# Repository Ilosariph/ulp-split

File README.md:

# ULP Split

Wireless split keyboard: 25 keys per half (6 columns, 4/4/4/4/3/3 + 3 thumbs), choc spacing (18 x 17 mm),
Cherry MX ULP switches (through-hole, double-sided footprint), Seeed XIAO nRF52840, ZMK.

## Layout

```
pcb/        ergogen config, footprints, autorouting + Gerber build
config/     ZMK keymap + conf (Colemak-DH-ish + Swiss German, ported from the tightarc Vial layout)
boards/     ZMK shield ulp_split (left = central)
case/       OpenSCAD tray case with 401525 LiPo pocket
```

## PCB

`pcb/build.sh` runs ergogen, autoroutes both halves with Freerouting, runs DRC and writes JLCPCB zips:

- `pcb/build/{left,right}.kicad_pcb` routed boards
- `pcb/build/jlcpcb-{left,right}.zip` Gerbers + drill

JLCPCB: 2 layers, 0.6 mm, LeadFree HASL, tented vias, Remove Mark.

Parts per half: 25 Cherry MX ULP, 25 1N4148WS (SOD-323, LCSC C2128), XIAO nRF52840, C&K PCM12SMTR power switch,
Molex 78171-0002 Pico-EZmate header + 36920-0200 cable (cut in half), LiPo with protection circuit (401525).
Trackpad half: 2x 4.7k 0805 (R1, R2).

Diodes sit on top, outside every keycap (strips at the column ends, beside the inner column, thumb gap), each
labelled with its key (column O/P/R/M/I/N/T + row T/H/B/L, thumbs TN/TM/TF; bar = cathode). The bottom only has
solder from the switch, battery and NFC pads. `pcb/place_diodes.py` picks the spots (>= 0.25 mm from the keycap
outlines, both halves) and rewrites the generated block in `config.yaml`; rerun it after `build.sh` when keys or parts
move, then build again.
Backup: SOD-123 pads (1N4148W, `DB*`) on the back under each switch, in parallel with the top diode. Fit one diode
per key. Back diodes need the 2 mm gap under the PCB; under the index-bottom and inner-home keys they sit close to
the `mount_opt` bosses, print the case with `use_opt = false` if you use those two.

## Case

`case/case.scad`: 4.8 mm tall tray (1.2 floor, 2 mm under the PCB, 0.6 PCB, 1 mm lip). The PCB drops in on a perimeter
ledge + a post under each key and is screwed down from the top: M2 x 4 screws into heat-set inserts (M2 x 3, 3.2 mm OD)
in bosses under the board (`screw_hole = 1.7` for self-tapping instead).
9 holes have the screw head clear of the keycaps (small tabs on the outer edge, gap above the thumbs, controller column).
7 more (`mount_opt_*`) sit between switch housings under the keycaps: only for low heads (wafer / ISO 7380), check
keycap clearance first; `use_opt = false` drops their bosses. The 401525 LiPo sits in its own pocket in the
notch between the far thumb key and the bottom of the controller column. The battery connector sits at the bottom edge of
the controller column with its plug facing the notch, so the wires drop straight into the pocket (no cable hole).
The notch takes a cell up to ~25 x 26 x 4 mm: set `bat` in `case.scad`. Openings for USB-C and the power switch lever.

```
openscad -o left.stl case/case.scad
openscad -D 'side="right"' -o right.stl case/case.scad
```

`case/pcb_left.dxf` is a copy of `pcb/output/outlines/left.dxf`; copy it again after changing the board outline.

## Matrix

col2row, 5 x 5 on D0..D9. Columns D0..D4 = outer, pinky, ring, middle, index.
Rows D7 top, D8 home, D9 bottom, D6 lower (outer 4 columns + near thumb on D4), D5 extra
(inner top/home/bottom on D3/D4/D2, mid thumb on D1, far thumb on D0).
D10 and the XIAO's NFC pads (NFC1 = P0.09, NFC2 = P0.10, plated through like the battery pads) drive the trackpad.

## Trackpad

Right half (firmware), pads on both: TP1 below the XIAO, 1x5 2.54 mm, GND / 3V3 / DR / SDA / SCL.
SDA = NFC1, SCL = NFC2 (UICR `nfct-pins-as-gpios`), DR = D10, R1/R2 = 4.7k 0805 pull-ups to 3V3.
Firmware: Cirque Pinnacle (`cirque,pinnacle` from petejohanson/cirque-input-module, I2C 0x2A) on the right half,
forwarded to the left through `zmk,input-split`. A TM040040 runs in I2C mode with R1 not fitted; wire VDD, GND, SCL,
SDA and DR from its test pads straight to TP1 (skip 5 V adapter boards). An Azoteq IQS5xx pad (TPS43/TPS65) fits
the same pads (RDY on DR, NRST tied to 3V3) with an IQS5xx driver module instead.

## Firmware

GitHub Actions builds `ulp_split_left`, `ulp_split_right` and `settings_reset` for `seeeduino_xiao_ble` (ZMK v0.3).
Flash: double-tap reset, copy the uf2 to the XIAO drive. Edit the keymap with https://nickcoutsos.github.io/keymap-editor.

The battery charges over USB only while the power switch is on (the switch sits between battery and XIAO).

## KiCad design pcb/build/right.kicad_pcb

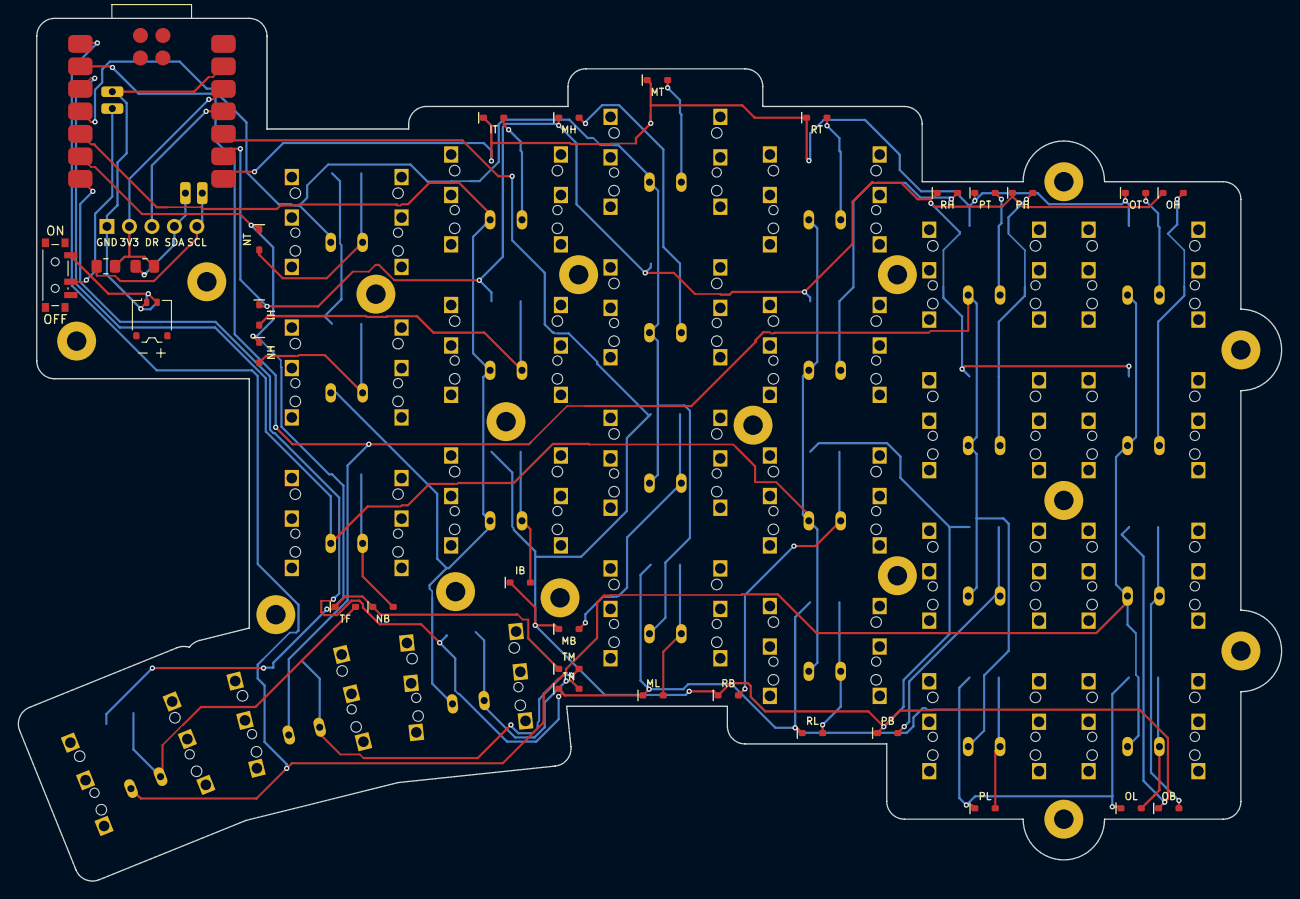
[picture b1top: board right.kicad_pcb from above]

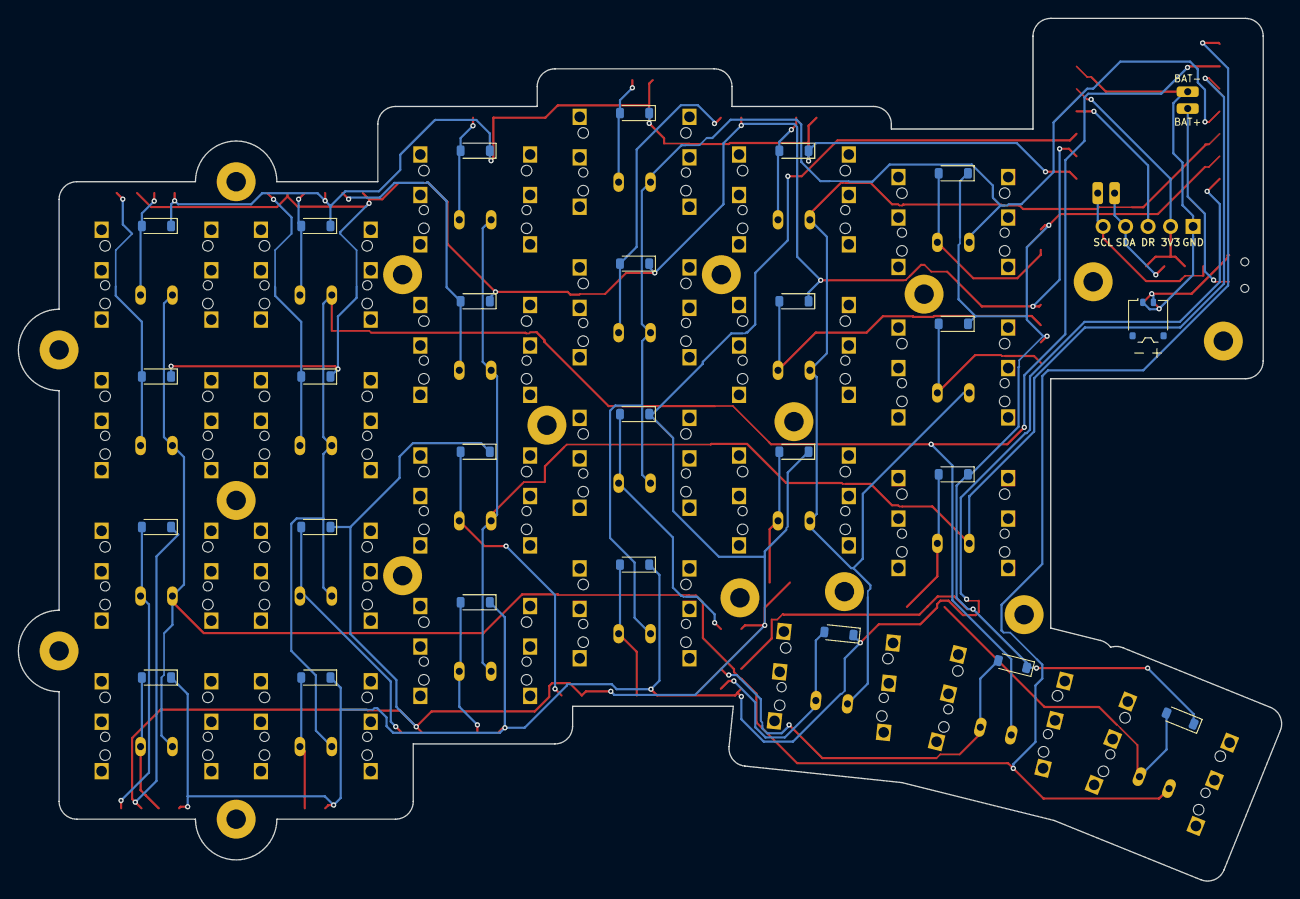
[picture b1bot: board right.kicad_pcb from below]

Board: 2 copper layers, 142.7 x 97.4 mm, 97 parts (25 on the bottom side), 42 nets.

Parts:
CONN1: battery_connector_molex_pico_ezmate_1x02
D1, D2, D3, D4, D5, D6, D7, D8, D9, D10, D11, D12, D13, D14, D15, D16, D17, D18, D19, D20, D21, D22, D23, D24, D25: D_SOD-323; D_SOD-323_Top
DB1, DB2, DB3, DB4, DB5, DB6, DB7, DB8, DB9, DB10, DB11, DB12, DB13, DB14, DB15, DB16, DB17, DB18, DB19, DB20, DB21, DB22, DB23, DB24, DB25: D_SOD-123; D_SOD-123_Back
H1, H2, H3, H4, H5, H6, H7, H8, H9, H10, H11, H12, H13, H14, H15, H16: mounting_hole_m2
MCU1: XIAO_nRF52840; Seeed_XIAO_nRF52840_SMD
PWR1: power_switch_smd_side
R1, R2: R_0805; R_0805_HandSolder
S1, S2, S3, S4, S5, S6, S7, S8, S9, S10, S11, S12, S13, S14, S15, S16, S17, S18, S19, S20, S21, S22, S23, S24, S25: Cherry_Ultra_Low_Profile_TH; Cherry_ULP_TH_Double_Sided
TP1: Trackpad_Pads_1x5

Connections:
3V3: MCU1.12, R1.2, R2.2, TP1.2
BAT: MCU1.19, PWR1.2
BAT_IN: CONN1.2, PWR1.1
D0: MCU1.1, S1.1, S2.1, S3.1, S4.1, S25.1
D1: MCU1.2, S5.1, S6.1, S7.1, S8.1, S24.1
D2: MCU1.3, S9.1, S10.1, S11.1, S12.1, S20.1
D3: MCU1.4, S13.1, S14.1, S15.1, S16.1, S22.1
D4: MCU1.5, S17.1, S18.1, S19.1, S21.1, S23.1
D5: D1.1, D5.1, D6.1, D7.1, D8.1, DB20.1, DB21.1, DB22.1, DB24.1, DB25.1, MCU1.6
D6: D11.1, D13.1, D16.1, D20.1, D24.1, DB1.1, DB5.1, DB9.1, DB13.1, DB23.1, MCU1.7
D7: D4.1, D12.1, D17.1, D21.1, D25.1, DB4.1, DB8.1, DB12.1, DB16.1, DB19.1, MCU1.8
D8: D3.1, D10.1, D15.1, D19.1, D23.1, DB3.1, DB7.1, DB11.1, DB15.1, DB18.1, MCU1.9
D9: D2.1, D9.1, D14.1, D18.1, D22.1, DB2.1, DB6.1, DB10.1, DB14.1, DB17.1, MCU1.10
D10: MCU1.11, TP1.3
GND: CONN1.1, MCU1.13, MCU1.20, TP1.1
SCL: MCU1.22, R2.1, TP1.5
SDA: MCU1.21, R1.1, TP1.4
mirror_far_cluster: D1.2, DB25.2, S25.2
mirror_index_bottom: D2.2, DB17.2, S17.2
mirror_index_home: D3.2, DB18.2, S18.2
mirror_index_top: D4.2, DB19.2, S19.2
mirror_inner_bottom: D5.2, DB20.2, S20.2
mirror_inner_home: D6.2, DB21.2, S21.2
mirror_inner_top: D7.2, DB22.2, S22.2
mirror_mid_cluster: D8.2, DB24.2, S24.2
mirror_middle_bottom: D9.2, DB14.2, S14.2
mirror_middle_home: D10.2, DB15.2, S15.2
mirror_middle_lower: D11.2, DB13.2, S13.2
mirror_middle_top: D12.2, DB16.2, S16.2
mirror_near_cluster: D13.2, DB23.2, S23.2
mirror_outer_bottom: D14.2, DB2.2, S2.2
mirror_outer_home: D15.2, DB3.2, S3.2
mirror_outer_lower: D16.2, DB1.2, S1.2
mirror_outer_top: D17.2, DB4.2, S4.2
mirror_pinky_bottom: D18.2, DB6.2, S6.2
mirror_pinky_home: D19.2, DB7.2, S7.2
mirror_pinky_lower: D20.2, DB5.2, S5.2
mirror_pinky_top: D21.2, DB8.2, S8.2
mirror_ring_bottom: D22.2, DB10.2, S10.2
mirror_ring_home: D23.2, DB11.2, S11.2
mirror_ring_lower: D24.2, DB9.2, S9.2
mirror_ring_top: D25.2, DB12.2, S12.2
